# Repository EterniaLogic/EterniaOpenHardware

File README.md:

Author: Brent Clancy

Email: brent.clancy@ttu.edu, eternialogic@gmail.com

Eternia's Open Hardware

License: LICENSE (TAPR Open Hardware License)

========================================================== 

MSP430 Dual Board - Provides a board that can take a transformer input at 120 V and converts it down to 12 V. This 12 V is then converted down to 3.3 V and 5 V for use with the MSP430G2553IN28, RAM and a DAC. (Digital-to-Analog Converter) This board provides up to 40 I/O, 2 ADCs, 1 DAC, 8Kb RAM, and Debugging ports for plugging into a TI debugger.

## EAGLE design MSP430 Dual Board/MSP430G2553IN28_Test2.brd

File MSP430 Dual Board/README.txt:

Tips for Programming:

I2C is used for communication in between the two MSP430s.

SPI is used to communicate with the DAC and the F-RAM chips.

The debugger input uses TEST and RST

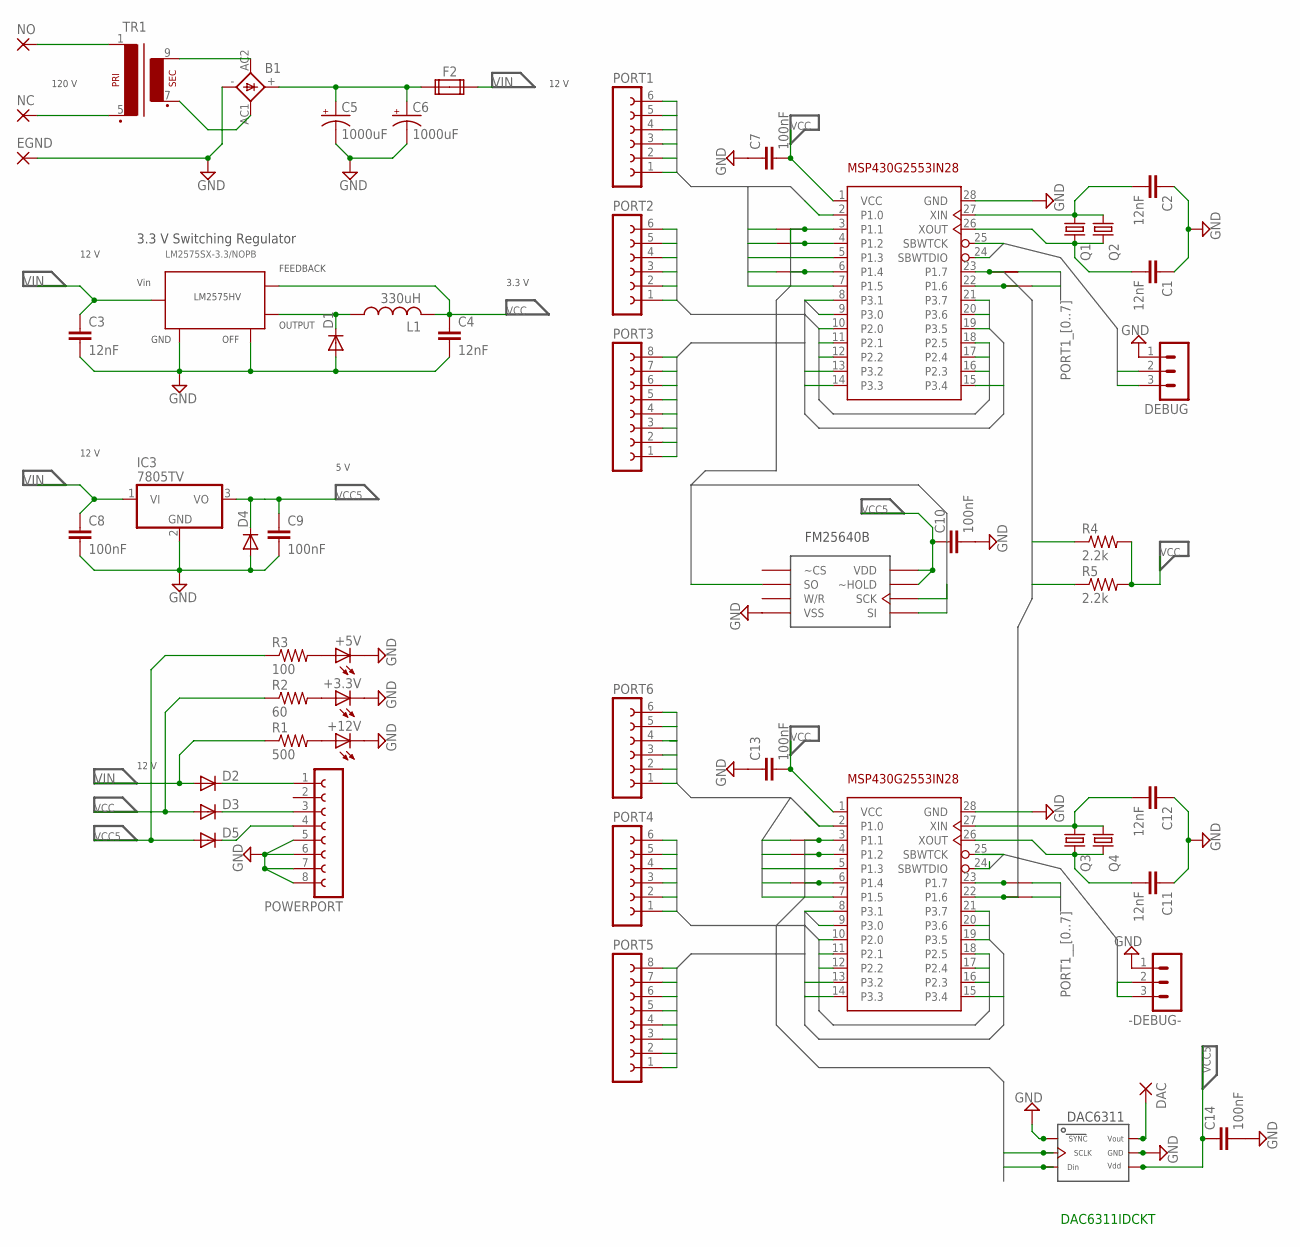
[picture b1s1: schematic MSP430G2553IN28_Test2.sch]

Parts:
+3.3V, +5V, +12V: LEDSML0603; SML0603
-DEBUG-: MA03-1
B1: GBU4; GBU4S
C1, C2, C3, C4, C11, C12: 12nF; C0402
C5, C6: 1000uF; E5-8,5
C7, C8, C9, C10, C13, C14: 100nF; C0402
D1, D4: DIODE-SOD106-R; SOD106-R
D2, D3, D5: DIODE-DO41-7.6; DO41-7.6
DAC: 1,6/0,8
DEBUG: MA03-1
EGND: 3,81/1,4
F2: FUSE2P; FUSE1
IC1, IC4: MSP430; P-TSSOP28-1
IC2: FM25640BSO8; SO08
IC3: 7805TV; TO220V
IC5: DAC6311; SC70-6
IC6: CUSTOM_REGULATOR; TO263-5
L1: 330uH; L1812
NC: 3,81/1,4
NO: 3,81/1,4
PORT1, PORT2, PORT4, PORT6: FE06-1; FE06
PORT3, PORT5: FE08-1; FE08
POWERPORT: FE08-1; FE08
Q1, Q3: CRYSTALTC26H; TC26H
Q2, Q4: CRYSTALHC49U-V; HC49U-V
R1: 500; R0402
R2: 60; R0402
R3: 100; R0402
R4, R5: 2.2k; R0402
TR1: VV11
U$1, U$6, U$7, U$8, U$9, U$10, U$11, U$12, U$13, U$14, U$15: SHORTSHORT; SMALLSHORT

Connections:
DEBUG_P1: DEBUG.2, IC1.25 (SBWTCK)
DEBUG_P2: DEBUG.3, IC1.24 (SBWTDIO)
DEBUG_P4: -DEBUG-.3, IC4.24 (SBWTDIO)
DEBUG_P_2: -DEBUG-.2, IC4.25 (SBWTCK)
GND: +3.3V.C, +5V.C, +12V.C, -DEBUG-.1, B1.-, C1.1, C2.1, C3.2, C4.2, C5.-, C6.-, C7.1, C8.2, C9.2, C10.2, C11.1, C12.1, C13.1, C14.2, D1.A, D4.A, DEBUG.1, EGND.1, IC1.28 (GND), IC2.4 (VSS), IC3.2 (GND), IC4.28 (GND), IC5.1, IC5.5, IC6.3, IC6.5, IC6.6, POWERPORT.5, POWERPORT.6, POWERPORT.7, POWERPORT.8
I2C0: IC1.23 (P1.7), IC4.23 (P1.7), R4.1, U$8.1, U$9.1, U$14.1
I2C1: IC1.22 (P1.6), IC4.22 (P1.6), R5.1, U$10.1, U$15.1
unnamed: C2.2, IC1.27 (XIN), Q1.1, Q2.1
unnamed: C1.2, IC1.26 (XOUT), Q1.2, Q2.2
unnamed: NC.1, TR1.5 (P2)
unnamed: NO.1, TR1.1
unnamed: +12V.A, R1.2
unnamed: +3.3V.A, R2.2
unnamed: D2.C, POWERPORT.1
unnamed: D3.C, POWERPORT.3
unnamed: B1.AC2 (AC1), TR1.9 (S4)
unnamed: B1.AC1 (AC2), TR1.7 (S3)
unnamed: C12.2, IC4.27 (XIN), Q3.1, Q4.1
unnamed: C11.2, IC4.26 (XOUT), Q3.2, Q4.2
unnamed: D5.C, POWERPORT.4
unnamed: +5V.A, R3.2
unnamed: DAC.1, IC5.6
unnamed: B1.+, C5.+, C6.+, F2.1A
P$2: D1.C, IC6.2, L1.1
PORT1_0: IC1.2 (P1.0), PORT1.1
PORT1_1: PORT1.2, U$1.1
PORT1_2: PORT1.3, U$6.1
PORT1_3: IC1.5 (P1.3), PORT1.4
PORT1_4: PORT1.5, U$7.1
PORT1_5: IC1.7 (P1.5), PORT1.6
PORT1_6: U$10.2
PORT1_7: U$8.2, U$9.2
PORT1__0: IC4.2 (P1.0), PORT6.1
PORT1__1: PORT6.2, U$11.1
PORT1__2: PORT6.3, U$12.1
PORT1__3: IC4.5 (P1.3), PORT6.4
PORT1__4: PORT6.5, U$13.1
PORT1__5: IC4.7 (P1.5), PORT6.6
PORT1__6: U$15.2
PORT1__7: U$14.2
PORT2_0: IC1.10 (P2.0), PORT2.1
PORT2_1: IC1.11 (P2.1), PORT2.2
PORT2_2: IC1.12 (P2.2), PORT2.3
PORT2_3: IC1.16 (P2.3), PORT2.4
PORT2_4: IC1.17 (P2.4), PORT2.5
PORT2_5: IC1.18 (P2.5), PORT2.6
PORT2_6: PORT4.1
PORT2__0: IC4.10 (P2.0)
PORT2__1: IC4.11 (P2.1), PORT4.2
PORT2__2: IC4.12 (P2.2), PORT4.3
PORT2__3: IC4.16 (P2.3), PORT4.4
PORT2__4: IC4.17 (P2.4), PORT4.5
PORT2__5: IC4.18 (P2.5), PORT4.6
PORT3_0: IC1.9 (P3.0), PORT3.1
PORT3_1: IC1.8 (P3.1), PORT3.2
PORT3_2: IC1.13 (P3.2), PORT3.3
PORT3_3: IC1.14 (P3.3), PORT3.4
PORT3_4: IC1.15 (P3.4), PORT3.5
PORT3_5: IC1.19 (P3.5), PORT3.6
PORT3_6: IC1.20 (P3.6), PORT3.7
PORT3_7: IC1.21 (P3.7), PORT3.8
PORT3__0: IC4.9 (P3.0), PORT5.1
PORT3__1: IC4.8 (P3.1), PORT5.2
PORT3__2: IC4.13 (P3.2), PORT5.3
PORT3__3: IC4.14 (P3.3), PORT5.4
PORT3__4: IC4.15 (P3.4), PORT5.5
PORT3__5: IC4.19 (P3.5), PORT5.6
PORT3__6: IC4.20 (P3.6), PORT5.7
PORT3__7: IC4.21 (P3.7), PORT5.8
SPI3: IC1.3 (P1.1), IC2.2 (SO), IC4.3 (P1.1), IC5.3, U$1.2, U$11.2
SPI4: IC1.4 (P1.2), IC2.5 (SI), IC4.4 (P1.2), U$6.2, U$12.2
SPI5: IC1.6 (P1.4), IC2.6 (SCK), IC4.6 (P1.4), IC5.2, U$7.2, U$13.2
VCC: C4.1, C7.2, C13.2, D3.A, IC1.1 (VCC), IC4.1 (VCC), IC6.4, L1.2, R2.1, R4.2, R5.2
VCC5: C9.1, C10.1, C14.1, D4.C, D5.A, IC2.7 (~HOLD), IC2.8 (VDD), IC3.3 (VO), IC5.4, R3.1
VIN: C3.1, C8.1, D2.A, F2.2A, IC3.1 (VI), IC6.1, R1.1

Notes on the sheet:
3.3 V Switching Regulator
LM2575SX-3.3/NOPB
120 V
12 V
3.3 V
5 V
DAC6311IDCKT

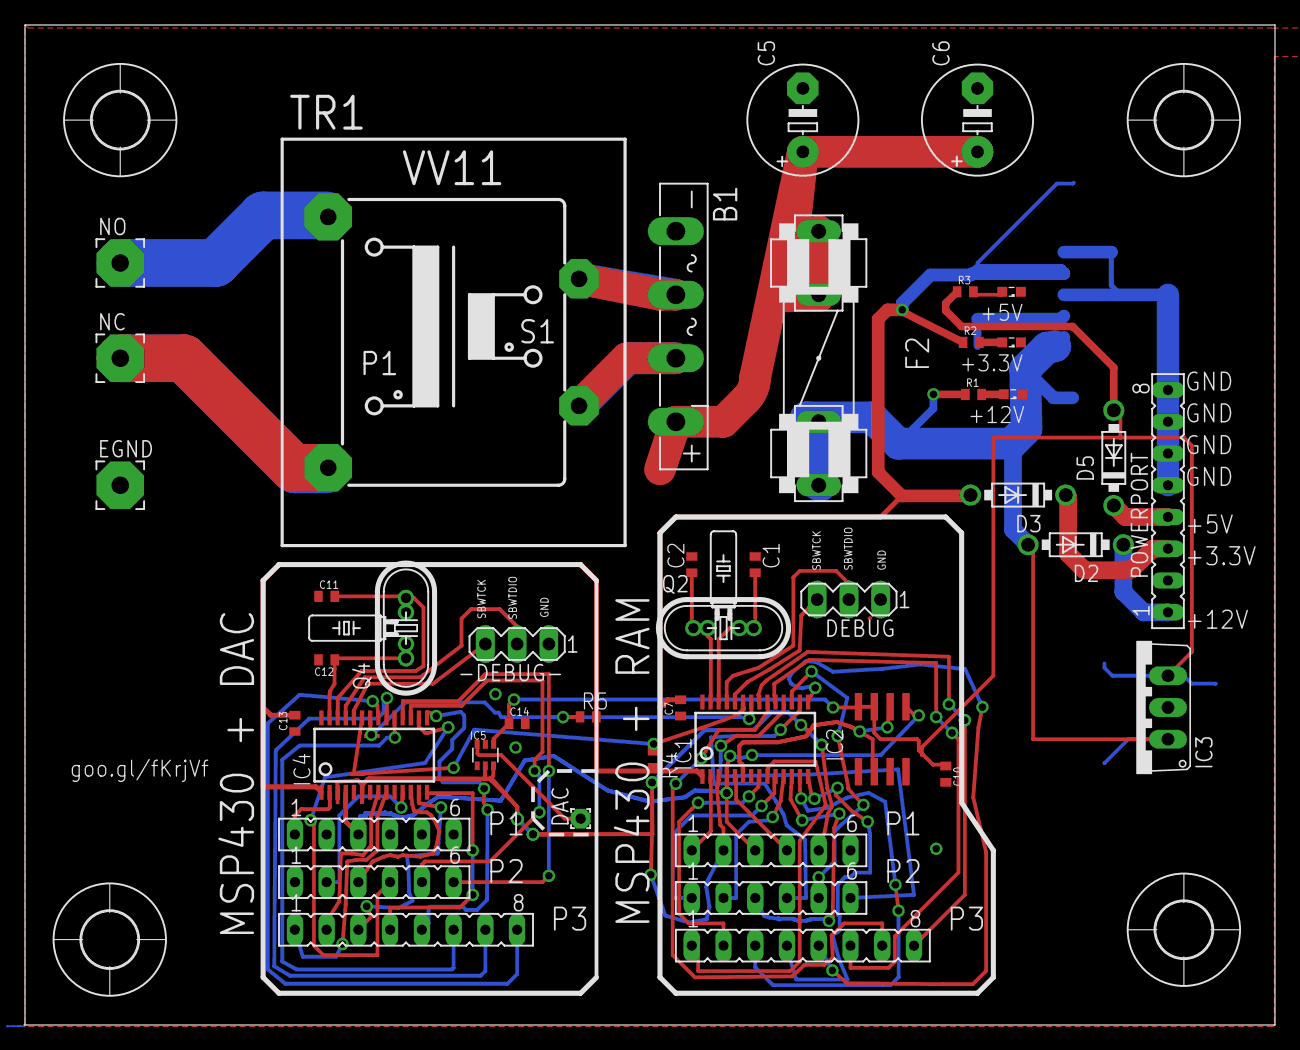
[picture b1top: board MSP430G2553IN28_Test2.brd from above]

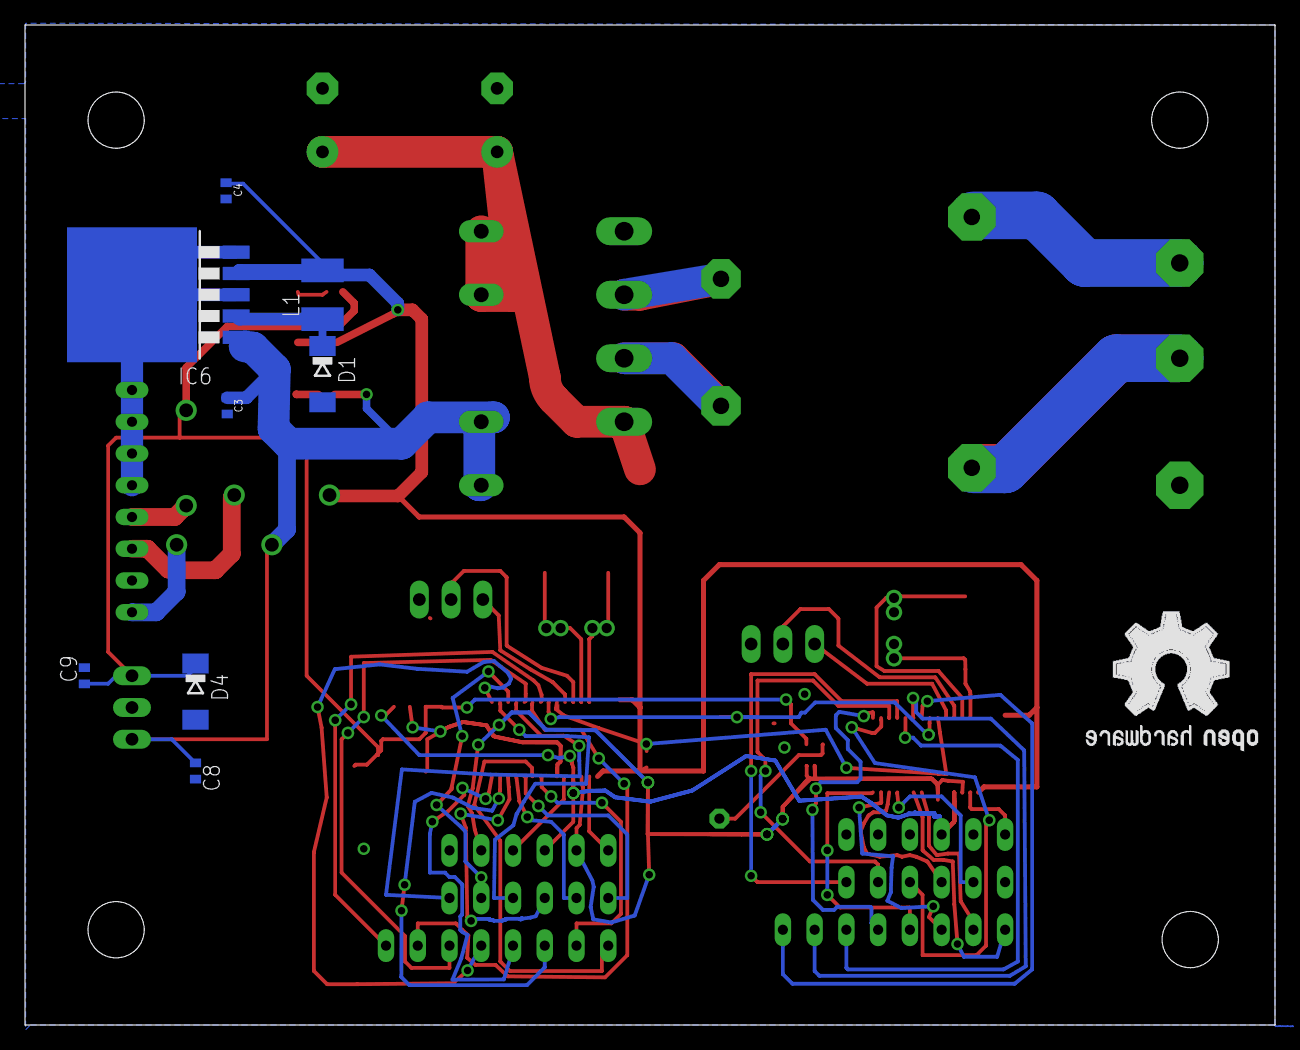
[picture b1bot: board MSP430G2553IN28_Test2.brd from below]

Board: 2 copper layers, 100.0 x 80.0 mm, 69 parts (8 on the bottom side), 70 nets.

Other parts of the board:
U$2, U$3, U$4, U$5: 4,5

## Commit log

2014-05-25 MSP430G2553IN28 Not fully Routed
2014-05-25 Added Open Hardware LOGO and github address
2014-05-25 Fully Routed MSP430 Dual Board
